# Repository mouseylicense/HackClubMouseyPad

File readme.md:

# BOM:
- 3x Gateron Milky Yellows
- 2x EC11 Encoder
- 1x PCB
- 1x I2C SSD1306 0.91" 128x32 OLED
- 4x 18mm M3 Screws

# Colors:
- Bottom Part in acrylic
- Middle Part in white
- Top  in Lime

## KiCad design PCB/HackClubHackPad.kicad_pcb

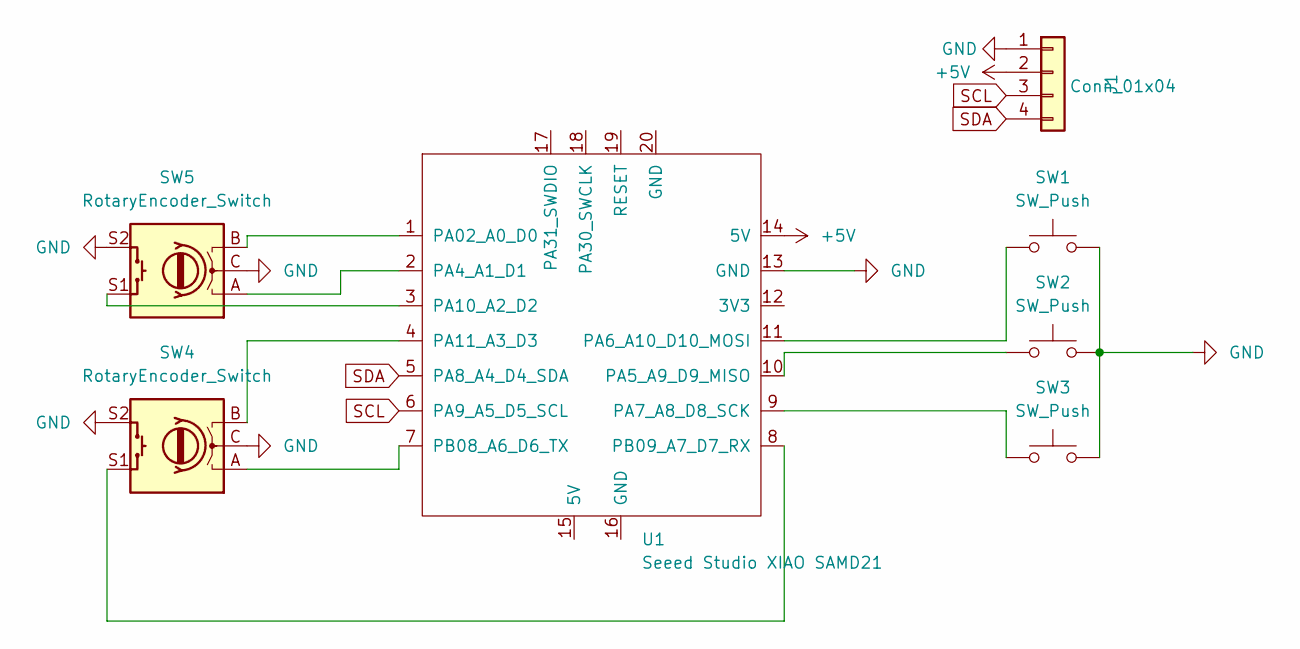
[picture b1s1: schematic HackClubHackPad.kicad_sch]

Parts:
J1: Conn_01x04; SSD1306-0.91-OLED-4pin-128x32
SW1, SW2, SW3: SW_Push; SW_Cherry_MX_1.00u_PCB
SW4, SW5: RotaryEncoder_Switch; RotaryEncoder_Alps_EC11E-Switch_Vertical_H20mm
U1: Seeed Studio XIAO SAMD21; XIAO-Generic-Thruhole-14P-2.54-21X17.8MM

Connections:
+5V: J1.2, U1.14 (5V)
GND: J1.1, SW1.2, SW2.2, SW3.2, SW4.C, SW4.S2, SW5.C, SW5.S2, U1.13 (GND)
unnamed: SW5.B, U1.1 (PA02_A0_D0)
unnamed: SW5.A, U1.2 (PA4_A1_D1)
unnamed: SW2.1, U1.10 (PA5_A9_D9_MISO)
unnamed: SW1.1, U1.11 (PA6_A10_D10_MOSI)
unnamed: SW3.1, U1.9 (PA7_A8_D8_SCK)
unnamed: SW5.S1, U1.3 (PA10_A2_D2)
unnamed: SW4.B, U1.4 (PA11_A3_D3)
unnamed: SW4.A, U1.7 (PB08_A6_D6_TX)
unnamed: SW4.S1, U1.8 (PB09_A7_D7_RX)
SCL: J1.3, U1.6 (PA9_A5_D5_SCL)
SDA: J1.4, U1.5 (PA8_A4_D4_SDA)

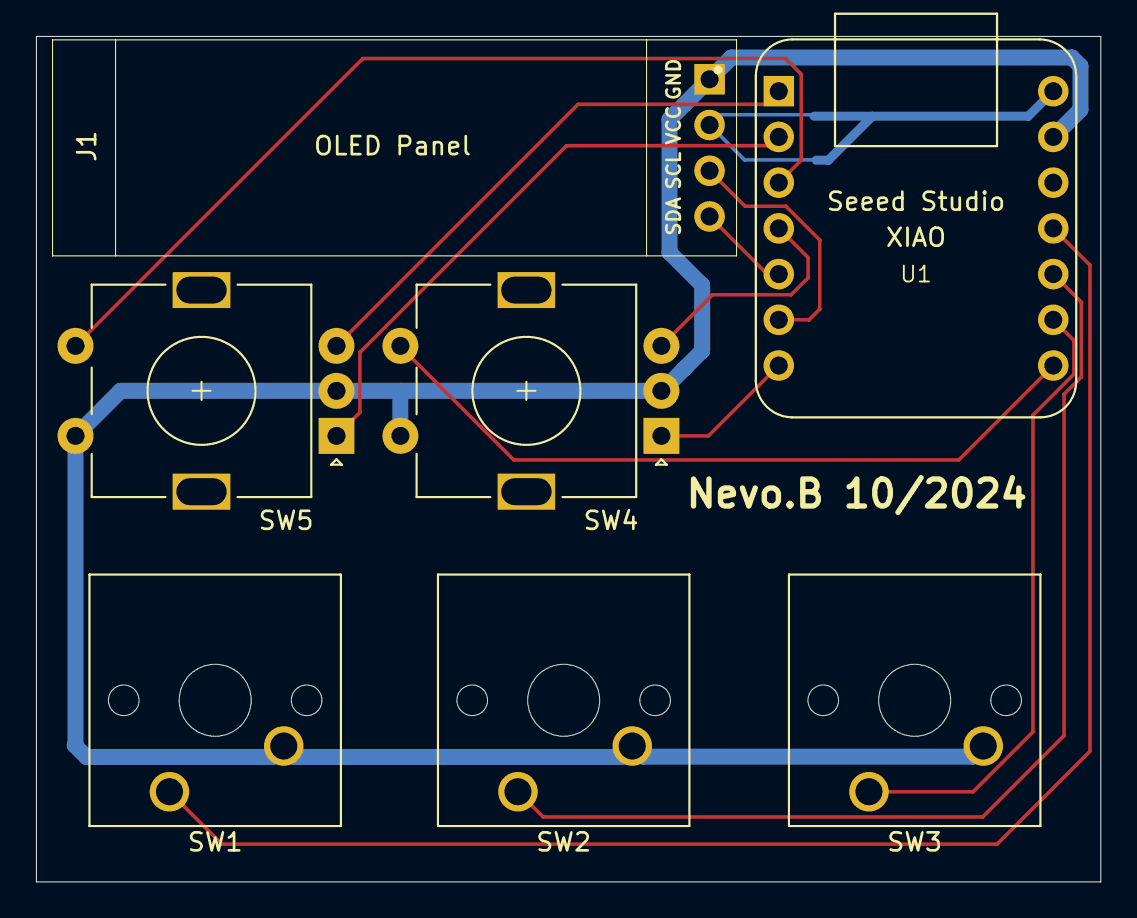
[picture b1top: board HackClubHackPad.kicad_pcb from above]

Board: 2 copper layers, 59.1 x 47.0 mm, 7 parts (0 on the bottom side), 13 nets.

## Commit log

2024-10-03 first commit, worked on pcb and firmware
2024-10-05 fixed firmware and changed pcb a bit
2024-10-05 Changed Board size and spacing
2024-10-09 Added VIA support (i think)
2024-10-09 Case for Pad
2024-10-09 edited cad and colors
2024-10-13 added binary (i think)
